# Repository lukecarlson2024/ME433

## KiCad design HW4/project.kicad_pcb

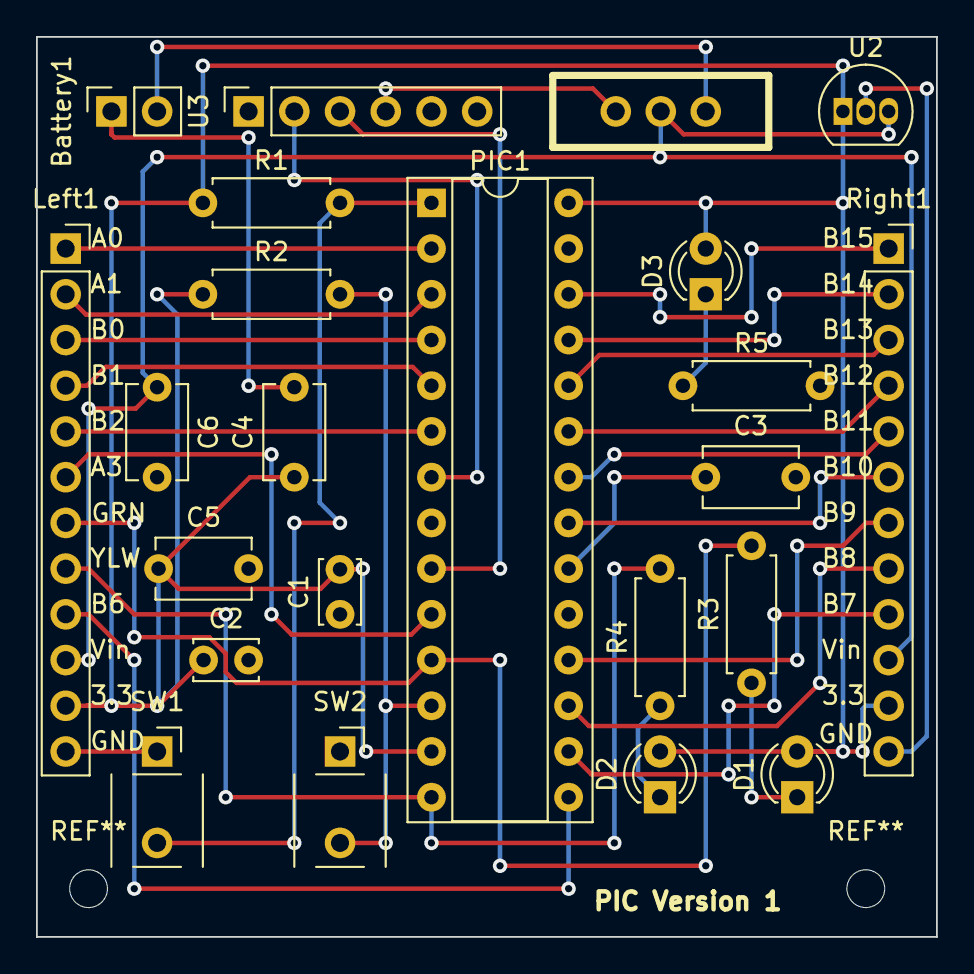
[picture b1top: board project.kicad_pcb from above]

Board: 2 copper layers, 50.0 x 50.0 mm, 23 parts (0 on the bottom side), 31 nets.

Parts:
Battery1: PinSocket_1x02_P2.54mm_Vertical
C1, C2: .1uF; C_Disc_D3.4mm_W2.1mm_P2.50mm
C3, C4, C5, C6: 1uF; C_Disc_D5.1mm_W3.2mm_P5.00mm
D1: GREEN; LED_D3.0mm
D2: YELLOW; LED_D3.0mm
D3: RED; LED_D3.0mm
Left1: PinSocket_1x12_P2.54mm_Vertical
PIC1: DIP-28_W7.62mm_Socket
R1, R2: 10k; R_Axial_DIN0207_L6.3mm_D2.5mm_P7.62mm_Horizontal
R3, R4, R5: 330; R_Axial_DIN0207_L6.3mm_D2.5mm_P7.62mm_Horizontal
Right1: PinSocket_1x12_P2.54mm_Vertical
SW1: MCLR; pinsocket push button
SW2: USER; pinsocket push button
SW3: SW_SPDT; slide_switch_2
U2: AP7381-3.3V; TO-92_Inline
U3: ADAfruit; PinSocket_1x06_P2.54mm_Vertical

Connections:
+3.3V: C1.2, C2.1, C4.1, C5.1, D1.2 (A), D2.2 (A), D3.2 (A), Left1.11, PIC1.13 (Vdd), PIC1.28 (AVdd), R1.1, R2.1, Right1.11, U2.1 (VO)
+5V: SW3.1 (A), U3.4 (5V)
/A0: Left1.1, PIC1.2 (A0)
/A1: Left1.2, PIC1.3 (A1)
/A3: Left1.6, PIC1.10 (A3)
/B0: Left1.3, PIC1.4 (B0)
/B1: Left1.4, PIC1.5 (B1)
/B2: Left1.5, PIC1.6 (B2)
/B6: Left1.9, PIC1.15 (B6)
/B7: PIC1.16 (B7), Right1.9
/B8: PIC1.17 (B8), Right1.8
/B9: PIC1.18 (B9), Right1.7
/B10: PIC1.21 (B10), Right1.6
/B11: PIC1.22 (B11), Right1.5
/B12: PIC1.23 (B12), Right1.4
/B13: PIC1.24 (B13), Right1.3
/B14: PIC1.25 (B14), Right1.2
/B15: PIC1.26 (B15), Right1.1
/GRN_LED: Left1.7, PIC1.11 (B4), R3.2
/MCLR: PIC1.1 (~MCLR), R1.2, SW1.2
/U1RX: PIC1.9 (A2), U3.3 (U1RX)
/U1TX: PIC1.7 (B3), U3.2 (U1TX)
/USER: PIC1.12 (A4), R2.2, SW2.2
/Vin: C6.1, Left1.10, Right1.10, SW3.2 (B), U2.3 (VI)
/YLW_LED: Left1.8, PIC1.14 (B5), R4.2
GND: Battery1.1, C1.1, C2.2, C3.2, C4.2, C5.2, C6.2, Left1.12, PIC1.8 (Vss), PIC1.19 (Vss), PIC1.27 (AVss), R5.2, Right1.12, SW1.1, SW2.1, U2.2 (GND), U3.6 (GND)
unnamed: Battery1.2, SW3.3 (C)
unnamed: D1.1 (K), R3.1
unnamed: D2.1 (K), R4.1
unnamed: D3.1 (K), R5.1
unnamed: C3.1, PIC1.20 (Vcap)

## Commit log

2023-04-12 Created using Colaboratory
2023-05-23 hw10
2023-05-25 hw11
2023-05-26 hw14
2023-06-08 hw15
2023-06-08 hw15 python
2023-06-08 HW16
